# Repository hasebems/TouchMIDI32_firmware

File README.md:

# TouchMIDI32_firmware

This software is released under the MIT License, see LICENSE.txt.

## Outline
TouchMIDI32_firmware is developed to provide as firmware of "TouchMIDI32".
TouchMIDI32 is a microcontroller board with a PSoC4 that has functionalities of
touch sensors, USB, I2C, and UART.
This firmware is aimed at outputing MIDI Message via USB when touch sensors react.

## Environment
These files are built under PSoC Creator(IDE).

## 概要
TouchMIDI32_firmwareは、TouchMIDI32のファームウェアとして供給するために開発されました。
TouchMIDI32は、PSoC4を搭載したマイコンボードで、タッチセンサ、USB、I2C、UARTなどの機能を持っています。
本ファームウェアでは、タッチセンサの操作によりUSBからMIDIメッセージが出力されます。

## 利用環境
これらのファイルはIDEである PSoC Creator 上でビルドします。

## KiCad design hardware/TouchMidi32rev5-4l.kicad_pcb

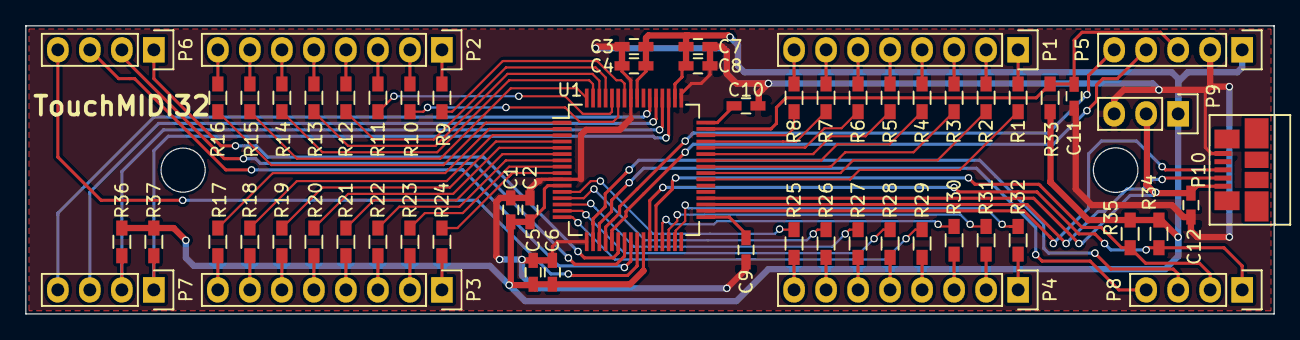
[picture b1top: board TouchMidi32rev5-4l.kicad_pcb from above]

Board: 2 copper layers, 99.1 x 22.9 mm, 60 parts (0 on the bottom side), 86 nets.

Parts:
C1, C3, C5, C7, C10: 1μF; C_0603_HandSoldering
C2, C4, C6, C8, C11, C12: 0.1μF; C_0603_HandSoldering
C9: 2.2nF; C_0603_HandSoldering
P1, P2, P3, P4: CONN_01X08; Pin_Header_Straight_1x08
P5: CONN_01X05; Pin_Header_Straight_1x05
P6, P7, P8: CONN_01X04; Pin_Header_Straight_1x04
P9: CONN_01X03; Pin_Header_Straight_1x03
P10: USB_B; USB_Micro-B(molex)
R1, R2, R3, R4, R5, R6, R7, R8, R9, R10, R11, R12, R13, R14, R15, R16, R17, R18, R19, R20, R21, R22, R23, R24, R25, R26, R27, R28, R29, R30, R31, R32: 560Ω; R_0603_HandSoldering
R33, R34, R35: 4.7kΩ; R_0603_HandSoldering
R36, R37: 10KΩ; R_0603_HandSoldering
U1: CY8C4246AZI-L445; TQFP-64_10x10mm_Pitch0.5mm

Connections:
/RES: C11.1, P5.3, R33.2, U1.47
GND: C1.2, C2.2, C3.2, C4.2, C5.2, C6.2, C7.2, C8.2, C9.2, C10.2, C11.2, C12.2, P5.2, P9.3, P10.5, U1.10, U1.17, U1.49, U1.57
unnamed: C9.1, U1.33
unnamed: C10.1, U1.48
unnamed: C12.1, P9.2, P10.1, U1.36
unnamed: P1.1, R1.1
unnamed: P1.2, R2.1
unnamed: P1.3, R3.1
unnamed: P1.4, R4.1
unnamed: P1.5, R5.1
unnamed: P1.6, R6.1
unnamed: P1.7, R7.1
unnamed: P1.8, R8.1
unnamed: P2.1, R9.2
unnamed: P2.2, R10.2
unnamed: P2.3, R11.2
unnamed: P2.4, R12.2
unnamed: P2.5, R13.2
unnamed: P2.6, R14.2
unnamed: P2.7, R15.2
unnamed: P2.8, R16.2
unnamed: P3.1, R24.2
unnamed: P3.2, R23.2
unnamed: P3.3, R22.2
unnamed: P3.4, R21.2
unnamed: P3.5, R20.2
unnamed: P3.6, R19.2
unnamed: P3.7, R18.2
unnamed: P3.8, R17.2
unnamed: P4.1, R32.2
unnamed: P4.2, R31.2
unnamed: P4.3, R30.2
unnamed: P4.4, R29.2
unnamed: P4.5, R28.2
unnamed: P4.6, R27.2
unnamed: P4.7, R26.2
unnamed: P4.8, R25.2
unnamed: P5.4, U1.21
unnamed: P5.5, U1.20
unnamed: P6.1, U1.22
unnamed: P6.2, U1.23
unnamed: P6.3, U1.24
unnamed: P6.4, U1.25
unnamed: P7.1, R37.2, U1.51
unnamed: P7.2, R36.2, U1.52
unnamed: P7.3, U1.53
unnamed: P7.4, U1.54
unnamed: P8.1, R34.2, U1.27
unnamed: P8.2, R35.2, U1.28
unnamed: P8.3, U1.18
unnamed: P8.4, U1.19
unnamed: P10.2, U1.35
unnamed: P10.3, U1.34
unnamed: R1.2, U1.39
unnamed: R2.2, U1.40
unnamed: R3.2, U1.41
unnamed: R4.2, U1.42
unnamed: R5.2, U1.43
unnamed: R6.2, U1.44
unnamed: R7.2, U1.45
unnamed: R8.2, U1.46
unnamed: R9.1, U1.58
unnamed: R10.1, U1.59
unnamed: R11.1, U1.60
unnamed: R12.1, U1.61
unnamed: R13.1, U1.62
unnamed: R14.1, U1.63
unnamed: R15.1, U1.64
unnamed: R16.1, U1.1
unnamed: R17.1, U1.2
unnamed: R18.1, U1.3
unnamed: R19.1, U1.4
unnamed: R20.1, U1.5
unnamed: R21.1, U1.6
unnamed: R22.1, U1.7
unnamed: R23.1, U1.8
unnamed: R24.1, U1.9
unnamed: R25.1, U1.12
unnamed: R26.1, U1.13
unnamed: R27.1, U1.14
unnamed: R28.1, U1.15
unnamed: R29.1, U1.16
unnamed: R30.1, U1.29
unnamed: R31.1, U1.30
unnamed: R32.1, U1.31
VDD: C1.1, C2.1, C3.1, C4.1, C5.1, C6.1, C7.1, C8.1, P5.1, P9.1, R33.1, R34.1, R35.1, R36.1, R37.1, U1.11, U1.26, U1.50, U1.56

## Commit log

2017-03-17 :octocat: Added .gitattributes
2017-03-17 1st Release
2017-03-17 手を入れた自動生成ソースを追加
2017-03-17 ライセンスとreadmeの追加
2017-03-19 coMIDIの調整
    CapSense Finger capasitance 0.8
    LEDの点灯調整
2017-03-22 MIDI Rx全体を#ifで切れるようにした
2017-03-28 TouchMidi32rev5-4l.pdf を追加
2017-03-31 自動生成ファイルを追加
2017-03-31 gitignoreを追加
2017-03-31 gitignoreにファイル追加
2017-03-31 VID/PID修正
2017-03-31 回路図のアップ
2017-04-11 フォルダ名の変更
    回路図とPCB設計資料を hardware というフォルダ名の下におくようにした
2017-04-11 ignoreのリストを完成させる
2017-04-24 Change project name from rev1 to main
2017-05-04 MagicFlute追加
    共通ソースをcommonフォルダに置く
2017-05-04 gitignore編集
2017-05-04 SwitchScienceへのTouchMIDI32製品出荷1st Version(5/4)
    MagicFluteにLPS25H（気圧センサ）のコードを足して、コンパイルエラーが取れたところまでの状態で、TouchMIDI32の出荷開始版として10枚書き込んだ。
2017-05-06 MagicFluteの実験基板で音が鳴った状態
    LPS25Hに変更
2017-06-03 HCB LED周りの実装
    PCA9685の追加に伴い、i2cdev.hを共通化し、各デバイスの有無をtm32_app.hに書くようにした。各プロジェクトのパス設定の順番も変更。
2017-06-03 PCA9685をPSoCで動作するように実装
2017-06-04 HoneycombBellのLED動作実装完了
    HoneycombBellのLED周りのバグ取りをして、動作するところまで実装した
2017-06-08 コネクション関連の処理を追加
    コネクションによって、オクターブを変化させる
    NonActiveのとき、LEDを点灯させない、タッチonの処理もしない
    NonActiveになったとき、AllKeyOffを送る
    KeyOffはその前にKeyOnになったものしか出さない
2017-06-10 fab13のプロジェクト追加、HCB機能追加
    ・竹村さん向けにfab13のプロジェクト追加（mainに気圧センサを追加した）
    ・HCB4のタッチの仕様に合わせたプログラムに修正
2017-06-11 fab13動作確認
    I2Cの設定がEZI2Cのままになっていたので、ピン配を修正
2017-06-15 タッチ位置の修正
    下段４セルのタッチ位置が左右逆になっていたので修正
2017-07-07 HCBの不具合修正
    オクターブの不具合
    Beat用ＬＥＤ処理修正
2017-07-11 HCB改良
    KeyOn時、二つの接点が同時に来ても一つしかKeyOnしないように修正。
    無発音時のLED点灯処理の改善。同じLEDが続けて光る場合も正常に動作するよう修正。
2017-09-18 FM音源用の準備でSPI追加
    YMF825Boardのための準備でSPIをPSoCに追加
2017-09-30 Start Terminal対応
    Start Terminal/Normal Block切り替えをポートで判断
2017-10-08 YMF825用のソースを追加
2017-10-29 完成したＨＣＢの動作チェックの不具合修正
    ・Note Onの行き先処理追加
    ・LED無発音パターン処理追加
    ・演奏以外のタッチスイッチ機能と表示処理追加
2017-11-01 無発音パターンの初期値はゼロにする
    テーブル値変更
2017-11-02 無発音パターンの変更
2018-03-03 25key追加
    TouchMIDIの新型25keyのプロジェクト作成
2018-03-08 音量調整
2018-03-18 音色変更、音量アップ
    音色を変更、オルガン増やし、パーカッションを削る
    音量を１２dBアップ
    音色切り替えが8音色で一回りするように修正
2018-04-21 音色変更など
    ＦＭ音源の音色変更
    ＭＩＤＩノート番号を１オクターブ低くする（結果的に鍵盤表示はヤマハ式でなくなる）
    ＬＥＤ３，４の役割変更
2018-05-26 add BLE Ocarina & adjust
